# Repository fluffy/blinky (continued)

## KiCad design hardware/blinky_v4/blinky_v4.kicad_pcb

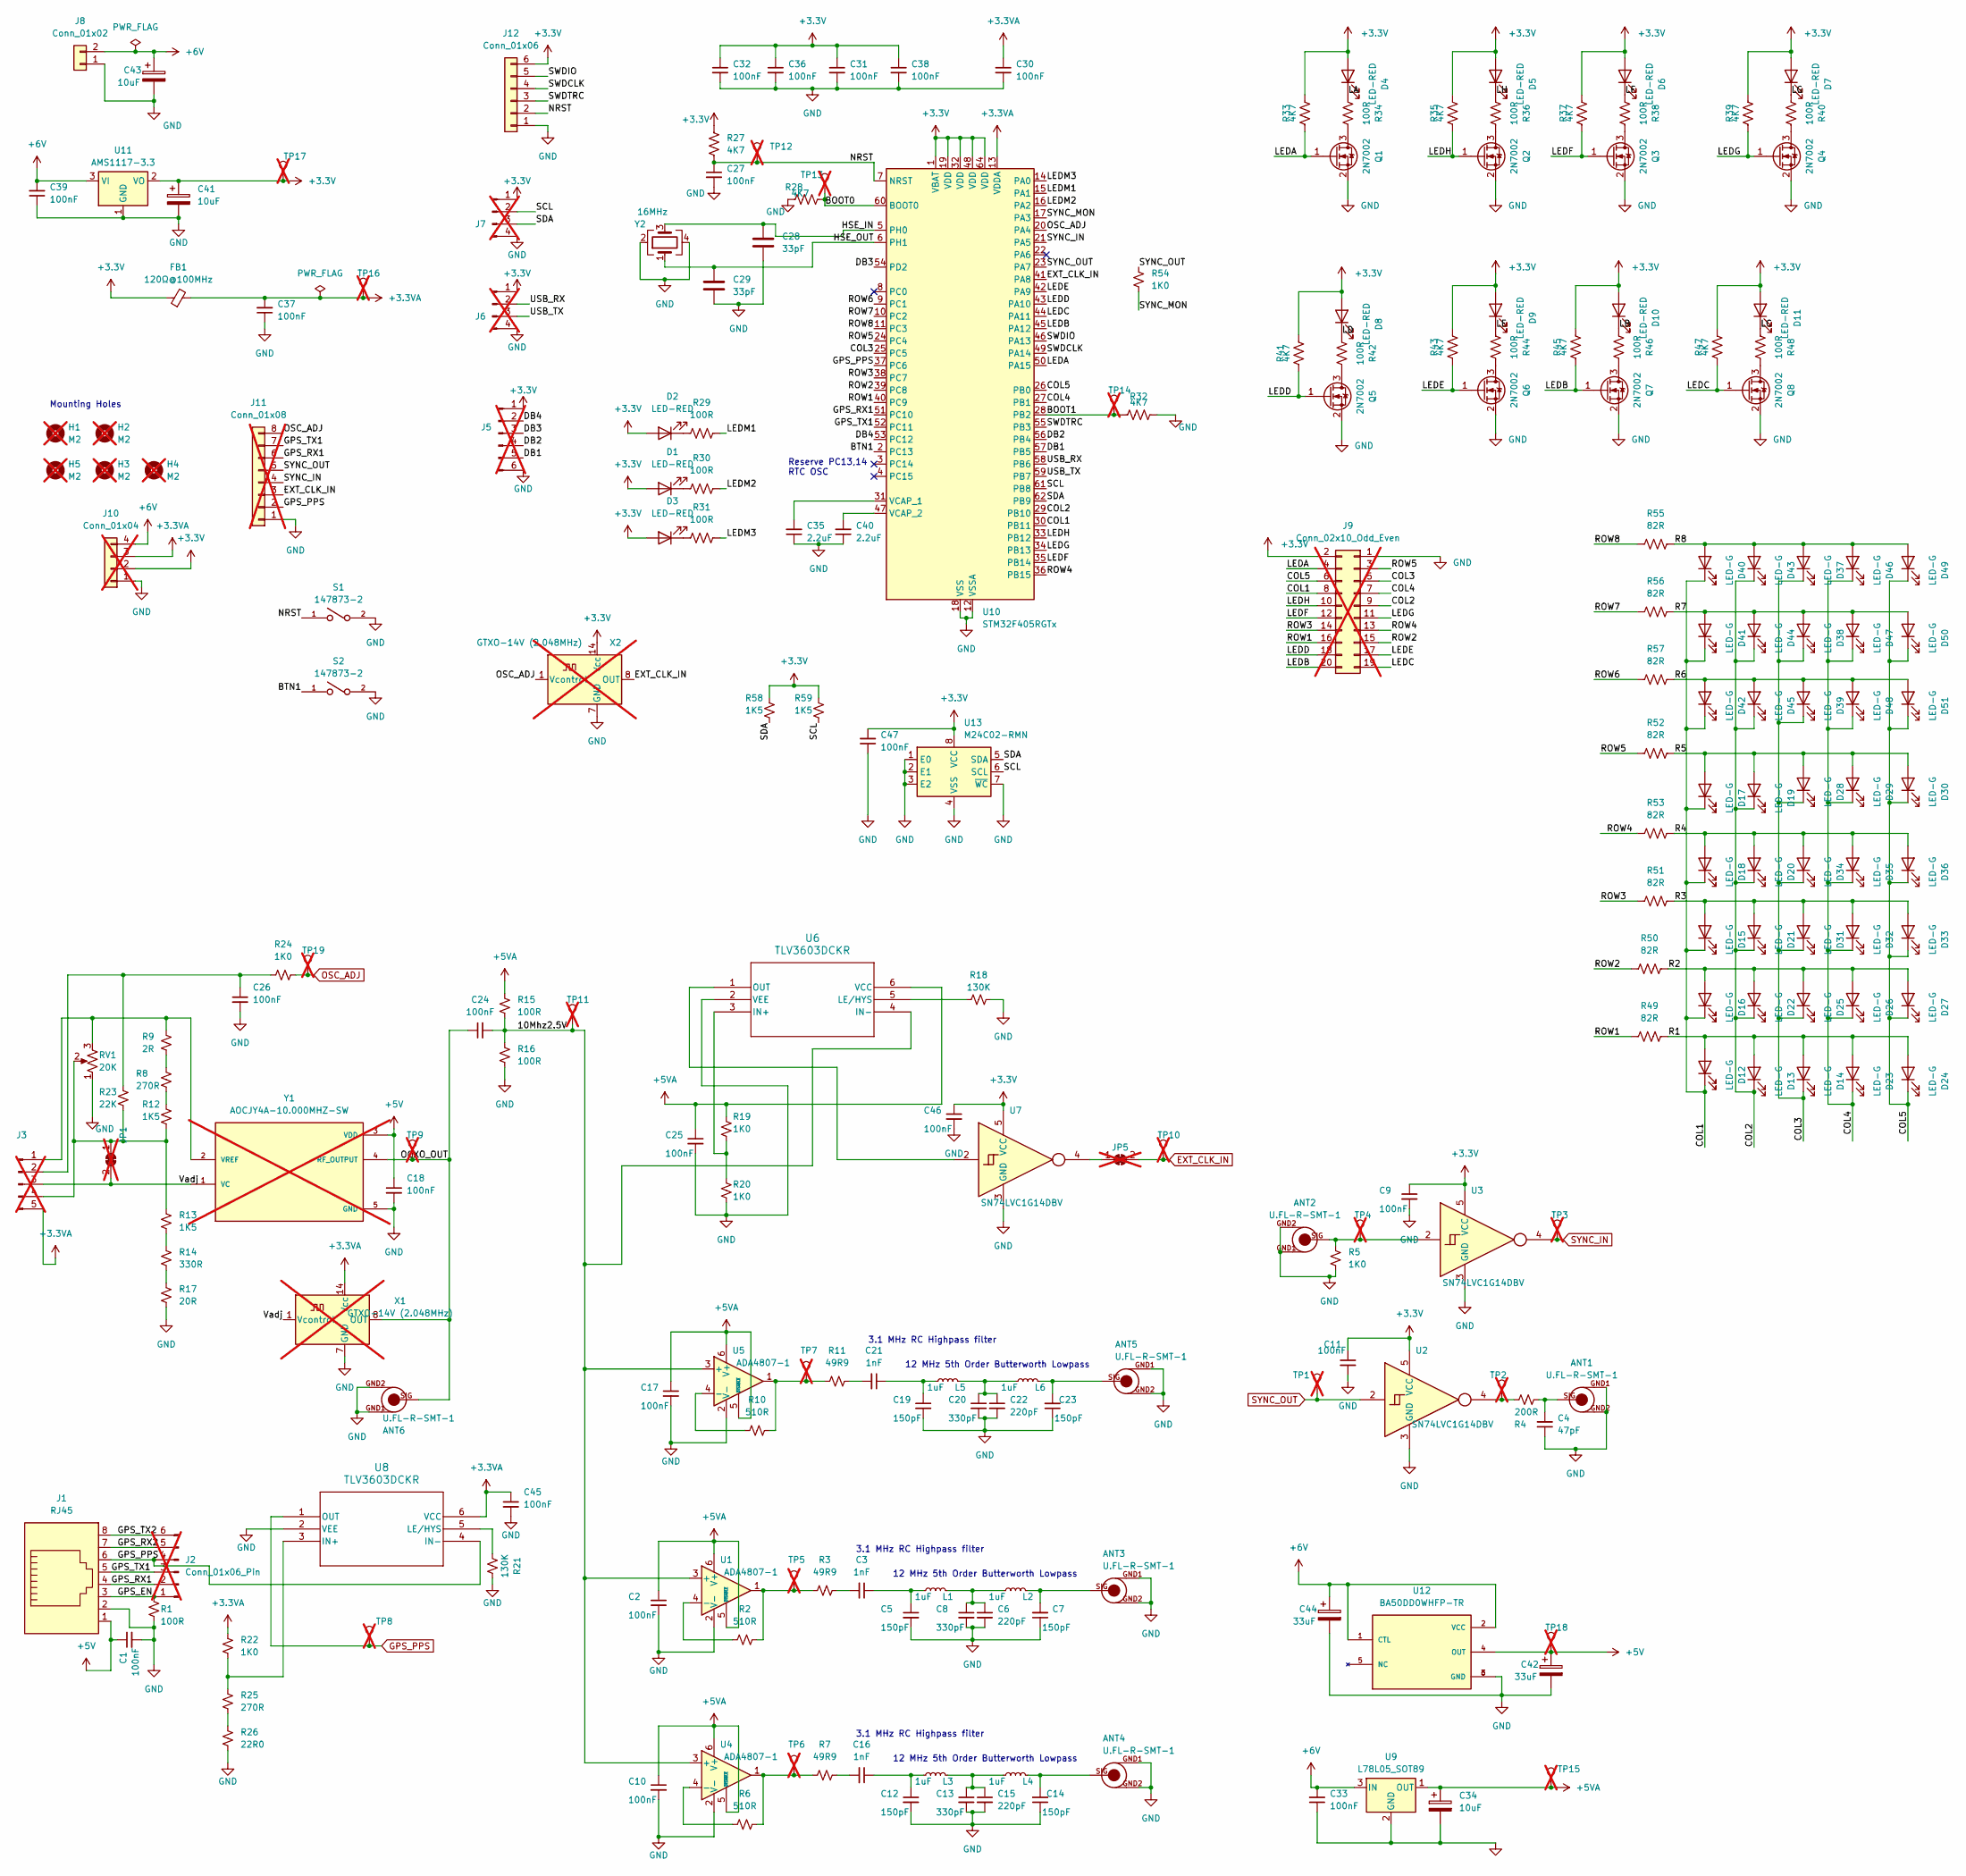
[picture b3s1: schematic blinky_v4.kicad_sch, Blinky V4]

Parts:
ANT1, ANT2, ANT3, ANT4, ANT5, ANT6: U.FL-R-SMT-1; LCSC C88374
C1, C2, C9, C10, C11, C17, C18, C25, C26, C30, C31, C32, C33, C36, C38, C39, C45, C46, C47: 100nF; C_0402_1005Metric; LCSC C307331
C3, C16, C21: 1nF; C_0603_1608Metric; LCSC C1588
C4: 47pF; C_0805_2012Metric; LCSC C14857
C5, C7, C12, C14, C19, C23: 150pF; C_0603_1608Metric; LCSC C1594
C6, C15, C22: 220pF; C_0603_1608Metric; LCSC C1603
C8, C13, C20: 330pF; C_0603_1608Metric; LCSC C1664
C24, C27, C37: 100nF; C_0603_1608Metric; LCSC C14663
C28, C29: 33pF; C_0603_1608Metric; LCSC C1663
C34, C41, C43: 10uF; CP_EIA-3216-18_Kemet-A; LCSC C7171
C35, C40: 2.2uF; C_0603_1608Metric; LCSC C23630
C42, C44: 33uF; CP_EIA-3528-21_Kemet-B; LCSC C128342
D1, D2, D3, D4, D5, D6, D7, D8, D9, D10, D11: LED-RED; LED_0603_1608Metric; LCSC C94869
D12, D13, D14, D15, D16, D17, D18, D19, D20, D21, D22, D23, D24, D25, D26, D27, D28, D29, D30, D31, D32, D33, D34, D35, D36, D37, D38, D39, D40, D41, D42, D43, D44, D45, D46, D47, D48, D49, D50, D51: LED-G; LED_0603_1608Metric; LCSC C125093
FB1: 120Ω@100MHz; R_0603_1608Metric; LCSC C127301
H1, H2, H3, H4, H5: M2; MountingHole_2.2mm_M2; not fitted
J1: RJ45; RJ45_Amphenol_RJHSE5380; LCSC C464586
J2, J5: Conn_01x06_Pin; PinHeader_1x06_P2.54mm_Vertical; not fitted
J3: Conn_01x05_Pin; PinHeader_1x05_P2.54mm_Vertical; not fitted
J6, J7: Conn_01x04_Pin; PinHeader_1x04_P2.54mm_Vertical; not fitted
J8: Conn_01x02; JST_PH_S2B-PH-SM4-TB_1x02-1MP_P2.00mm_Horizontal; LCSC C295747
J9: Conn_02x10_Odd_Even; PinHeader_2x10_P2.54mm_Vertical; not fitted
J10: Conn_01x04; PinHeader_1x04_P2.54mm_Vertical; not fitted
J11: Conn_01x08; PinHeader_1x08_P2.54mm_Vertical; not fitted
J12: Conn_01x06; JST_PH_S6B-PH-SM4-TB_1x06-1MP_P2.00mm_Horizontal; LCSC C265405
JP1, JP5: SolderJumper_2_Bridged; SolderJumper-2_P1.3mm_Bridged_RoundedPad1.0x1.5mm; not fitted
L1, L2, L3, L4, L5, L6: 1uF; L_0805_2012Metric; LCSC C1042
Q1, Q2, Q3, Q4, Q5, Q6, Q7, Q8: 2N7002; SOT-23; LCSC C8545
R1, R15, R16, R29, R30, R31, R34, R36, R38, R40, R42, R44, R46, R48: 100R; R_0603_1608Metric; LCSC C22775
R2, R6, R10: 510R; R_0603_1608Metric; LCSC C23193
R3, R7, R11: 49R9; R_0603_1608Metric; LCSC C23185
R4: 200R; R_0805_2012Metric; LCSC C17540
R5, R19, R20, R22, R24, R54: 1K0; R_0603_1608Metric; LCSC C21190
R8: 270R; R_0805_2012Metric; LCSC C17590
R9: 2R; R_0805_2012Metric; LCSC C17606
R12, R13: 1K5; R_0805_2012Metric; LCSC C4310
R14: 330R; R_0805_2012Metric; LCSC C17630
R17: 20R; R_0805_2012Metric; LCSC C17544
R18, R21: 130K; R_0603_1608Metric; LCSC C22795
R23: 22K; R_0805_2012Metric; LCSC C17560
R25: 270R; R_0603_1608Metric; LCSC C22966
R26: 22R0; R_0603_1608Metric; LCSC C23345
R27, R28, R32, R33, R35, R37, R39, R41, R43, R45, R47: 4K7; R_0603_1608Metric; LCSC C23162
R49, R50, R51, R52, R53, R55, R56, R57: 82R; R_0603_1608Metric; LCSC C23255
R58, R59: 1K5; R_0603_1608Metric; LCSC C22843
RV1: 20K; Potentiometer_Bourns_3314G_Vertical; LCSC C780217
S1, S2: 147873-2; SW_147873-2
TP1, TP2, TP3, TP4, TP5, TP6, TP7, TP8, TP9, TP10, TP11, TP12, TP13, TP14, TP15, TP16, TP17, TP18, TP19: TestPoint_THTPad_D1.5mm_Drill0.7mm; not fitted
U1, U4, U5: ADA4807-1; SOT-23-6; LCSC C2058411
U2, U3, U7: SN74LVC1G14DBV; SOT-23-5; LCSC C133145
U6, U8: TLV3603DCKR; SC70_DCK_TEX; LCSC C5213955
U9: L78L05_SOT89; SOT-89-3; LCSC C71136
U10: STM32F405RGTx; LQFP-64_10x10mm_P0.5mm; LCSC C15742
U11: AMS1117-3.3; SOT-223-3_TabPin2; LCSC C6186
U12: BA50DD0WHFP-TR; DPAK172P1054X200-6N; PARTREV 003; LCSC C509718
U13: M24C02-RMN; SOIC-8_3.9x4.9mm_P1.27mm; LCSC C83836
X1, X2: GTXO-14V (2.048MHz); Oscillator_DIP-14; not fitted
Y1: AOCJY4A-10.000MHZ-SW; XTAL_AOCJY4A-10.000MHZ-SW; PARTREV 07.24.11; LCSC C1670487; not fitted
Y2: 16MHz; Crystal_SMD_3225-4Pin_3.2x2.5mm; LCSC C13738

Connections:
+3.3V: C9.1, C11.1, C31.1, C32.1, C36.1, C38.1, C41.1, C46.1, C47.2, D1.2 (A), D2.2 (A), D3.2 (A), D4.2 (A), D5.2 (A), D6.2 (A), D7.2 (A), D8.2 (A), D9.2 (A), D10.2 (A), D11.2 (A), FB1.1, J5.1, J6.1, J7.1, J9.2, J10.2, J12.6, R27.1, R33.1, R35.1, R37.1, R39.1, R41.1, R43.1, R45.1, R47.1, R58.1, R59.1, TP17.1, U2.5 (VCC), U3.5 (VCC), U7.5 (VCC), U10.1 (VBAT), U10.19 (VDD), U10.32 (VDD), U10.48 (VDD), U10.64 (VDD), U11.2 (VO), U13.8 (VCC), X2.14 (Vcc)
+3.3VA: C30.1, C37.2, C45.1, FB1.2, J3.5, J10.3, R22.1, TP16.1, U8.6 (VCC), U10.13 (VDDA), X1.14 (Vcc)
+5V: C1.1, C18.1, C42.1, J1.1, TP18.1, U12.4 (OUT), Y1.3 (VDD)
+5VA: C2.1, C10.1, C17.1, C25.1, C34.1, R15.1, R19.1, TP15.1, U1.5 (~DISABLE), U1.6 (V+), U4.5 (~DISABLE), U4.6 (V+), U5.5 (~DISABLE), U5.6 (V+), U6.6 (VCC), U9.1 (OUT)
+6V: C33.2, C39.2, C43.1, C44.1, J8.2, J10.4, U9.3 (IN), U11.3 (VI), U12.1 (CTL), U12.2 (VCC)
/10Mhz2.5V: C24.2, R15.2, R16.1, TP11.1, U1.3 (+), U4.3 (+), U5.3 (+), U6.4 (IN-)
/BOOT0: R28.1, TP13.1, U10.60 (BOOT0)
/BOOT1: R32.2, TP14.1, U10.28 (PB2)
/BTN1: S2.1, U10.2 (PC13)
/COL1: D12.1 (K), D15.1 (K), D16.1 (K), D17.1 (K), D18.1 (K), D40.1 (K), D41.1 (K), D42.1 (K), J9.8, U10.30 (PB11)
/COL2: D13.1 (K), D19.1 (K), D20.1 (K), D21.1 (K), D22.1 (K), D43.1 (K), D44.1 (K), D45.1 (K), J9.9, U10.29 (PB10)
/COL3: D14.1 (K), D25.1 (K), D28.1 (K), D31.1 (K), D34.1 (K), D37.1 (K), D38.1 (K), D39.1 (K), J9.5, U10.25 (PC5)
/COL4: D23.1 (K), D26.1 (K), D29.1 (K), D32.1 (K), D35.1 (K), D46.1 (K), D47.1 (K), D48.1 (K), J9.7, U10.27 (PB1)
/COL5: D24.1 (K), D27.1 (K), D30.1 (K), D33.1 (K), D36.1 (K), D49.1 (K), D50.1 (K), D51.1 (K), J9.6, U10.26 (PB0)
/DB1: J5.5, U10.57 (PB5)
/DB2: J5.4, U10.56 (PB4)
/DB3: J5.3, U10.54 (PD2)
/DB4: J5.2, U10.53 (PC12)
/GPS_EN: J1.3, J2.1, R1.1
/GPS_RX1: J1.4, J2.2, J11.6, U10.51 (PC10)
/GPS_RX2: J1.7, J2.5
/GPS_TX1: J1.5, J2.3, J11.7, U10.52 (PC11)
/GPS_TX2: J1.8, J2.6
/HSE_IN: C28.1, U10.5 (PH0), Y2.3
/HSE_OUT: C29.1, U10.6 (PH1), Y2.1
/LA: D4.1 (K), R34.1
/LB: D10.1 (K), R46.1
/LC: D11.1 (K), R48.1
/LD: D8.1 (K), R42.1
/LE: D9.1 (K), R44.1
/LEDA: J9.4, Q1.1 (G), R33.2, U10.50 (PA15)
/LEDB: J9.20, Q7.1 (G), R45.2, U10.45 (PA12)
/LEDC: J9.19, Q8.1 (G), R47.2, U10.44 (PA11)
/LEDD: J9.18, Q5.1 (G), R41.2, U10.43 (PA10)
/LEDE: J9.17, Q6.1 (G), R43.2, U10.42 (PA9)
/LEDF: J9.12, Q3.1 (G), R37.2, U10.35 (PB14)
/LEDG: J9.11, Q4.1 (G), R39.2, U10.34 (PB13)
/LEDH: J9.10, Q2.1 (G), R35.2, U10.33 (PB12)
/LEDM1: R29.2, U10.15 (PA1)
/LEDM2: R30.2, U10.16 (PA2)
/LEDM3: R31.2, U10.14 (PA0)
/LF: D6.1 (K), R38.1
/LG: D7.1 (K), R40.1
/LH: D5.1 (K), R36.1
/NRST: C27.1, J12.2, R27.2, S1.1, TP12.1, U10.7 (NRST)
/OCXO_OUT: ANT6.SIG, C24.1, TP9.1, X1.8 (OUT), Y1.4 (RF_OUTPUT)
/R1: D12.2 (A), D13.2 (A), D14.2 (A), D23.2 (A), D24.2 (A), R49.1
/R2: D16.2 (A), D22.2 (A), D25.2 (A), D26.2 (A), D27.2 (A), R50.1
/R3: D15.2 (A), D21.2 (A), D31.2 (A), D32.2 (A), D33.2 (A), R51.1
/R4: D18.2 (A), D20.2 (A), D34.2 (A), D35.2 (A), D36.2 (A), R53.1
/R5: D17.2 (A), D19.2 (A), D28.2 (A), D29.2 (A), D30.2 (A), R52.1
/R6: D39.2 (A), D42.2 (A), D45.2 (A), D48.2 (A), D51.2 (A), R57.1
/R7: D38.2 (A), D41.2 (A), D44.2 (A), D47.2 (A), D50.2 (A), R56.1
/R8: D37.2 (A), D40.2 (A), D43.2 (A), D46.2 (A), D49.2 (A), R55.1
/ROW1: J9.16, R49.2, U10.40 (PC9)
/ROW2: J9.15, R50.2, U10.39 (PC8)
/ROW3: J9.14, R51.2, U10.38 (PC7)
/ROW4: J9.13, R53.2, U10.36 (PB15)
/ROW5: J9.3, R52.2, U10.24 (PC4)
/ROW6: R57.2, U10.9 (PC1)
/ROW7: R56.2, U10.10 (PC2)
/ROW8: R55.2, U10.11 (PC3)
/SCL: J7.2, R59.2, U10.61 (PB8), U13.6 (SCL)
/SDA: J7.3, R58.2, U10.62 (PB9), U13.5 (SDA)
/SWDCLK: J12.4, U10.49 (PA14)
/SWDIO: J12.5, U10.46 (PA13)
/SWDTRC: J12.3, U10.55 (PB3)
/SYNC_MON: R54.2, U10.17 (PA3)
/USB_RX: J6.2, U10.58 (PB6)
/USB_TX: J6.3, U10.59 (PB7)
/Vadj: J3.3, JP1.2 (B), X1.1 (Vcontrol), Y1.1 (VC)
EXT_CLK_IN: J11.3, JP5.2 (B), TP10.1, U10.41 (PA8), X2.8 (OUT)
GND: ANT1.GND1, ANT1.GND2, ANT2.GND1, ANT2.GND2, ANT3.GND1, ANT3.GND2, ANT4.GND1, ANT4.GND2, ANT5.GND1, ANT5.GND2, ANT6.GND1, ANT6.GND2, C1.2, C2.2, C4.1, C5.2, C6.2, C7.1, C8.2, C9.2, C10.2, C11.2, C12.2, C13.2, C14.1, C15.2, C17.2, C18.2, C19.2, C20.2, C22.2, C23.1, C25.2, C26.2, C27.2, C28.2, C29.2, C30.2, C31.2, C32.2, C33.1, C34.2, C35.1, C36.2, C37.1, C38.2, C39.1, C40.1, C41.2, C42.2, C43.2, C44.2, C45.2, C46.2, C47.1, J1.2, J5.6, J6.4, J7.4, J8.1, J9.1, J10.1, J11.1, J12.1, Q1.2 (S), Q2.2 (S), Q3.2 (S), Q4.2 (S), Q5.2 (S), Q6.2 (S), Q7.2 (S), Q8.2 (S), R1.2, R5.2, R16.2, R17.2, R18.2, R20.2, R21.2, R26.2, R28.2, R32.1, RV1.1, S1.2, S2.2, U1.2 (V-), U2.3 (GND), U3.3 (GND), U4.2 (V-), U5.2 (V-), U6.2 (VEE), U7.3 (GND), U8.2 (VEE), U9.2 (GND), U10.12 (VSSA), U10.18 (VSS), U10.63 (VSS), U11.1 (GND), U12.3 (GND), U12.6 (GND), U13.1 (E0), U13.2 (E1), U13.3 (E2), U13.4 (VSS), U13.7 (~WC), X1.7 (GND), X2.7 (GND), Y1.5 (GND), Y2.2, Y2.4
GPS_PPS: J1.6, J2.4, J11.2, TP8.1, U8.1 (OUT), U8.4 (IN-), U10.37 (PC6)
unnamed: ANT1.SIG, C4.2, R4.2
unnamed: ANT2.SIG, R5.1, TP4.1, U3.2
unnamed: ANT3.SIG, C7.2, L2.1
unnamed: ANT4.SIG, C14.2, L4.1
unnamed: ANT5.SIG, C23.2, L6.1
unnamed: C3.1, C5.1, L1.1
unnamed: C3.2, R3.2
unnamed: C6.1, C8.1, L1.2, L2.2
unnamed: C12.1, C16.1, L3.1
unnamed: C13.1, C15.1, L3.2, L4.2
unnamed: C16.2, R7.2
unnamed: C19.1, C21.1, L5.1
unnamed: C20.1, C22.1, L5.2, L6.2
unnamed: C21.2, R11.2
unnamed: D1.1 (K), R30.1
unnamed: D2.1 (K), R29.1
unnamed: D3.1 (K), R31.1
unnamed: J3.1, R9.1, RV1.3, Y1.2 (VREF)
unnamed: C26.1, J3.2, R23.1, R24.1
unnamed: J3.4, JP1.1 (A), R12.2, R13.1, R23.2, RV1.2
unnamed: JP5.1 (A), U7.4
unnamed: Q1.3 (D), R34.2
unnamed: Q2.3 (D), R36.2
unnamed: Q3.3 (D), R38.2
unnamed: Q4.3 (D), R40.2
unnamed: Q5.3 (D), R42.2
unnamed: Q6.3 (D), R44.2
unnamed: Q7.3 (D), R46.2
unnamed: Q8.3 (D), R48.2
unnamed: R2.2, R3.1, TP5.1, U1.1
unnamed: R4.1, TP2.1, U2.4
unnamed: R6.2, R7.1, TP6.1, U4.1
unnamed: R8.1, R9.2
unnamed: R10.2, R11.1, TP7.1, U5.1
unnamed: R8.2, R12.1
unnamed: R13.2, R14.1
unnamed: R14.2, R17.1
unnamed: R25.2, R26.1
unnamed: R2.1, U1.4 (-)
unnamed: R6.1, U4.4 (-)
unnamed: R10.1, U5.4 (-)
unnamed: R19.2, R20.1, U6.3 (IN+)
unnamed: R18.1, U6.5 (LE/HYS)
unnamed: U6.1 (OUT), U7.2
unnamed: R22.2, R25.1, U8.3 (IN+)
unnamed: R21.1, U8.5 (LE/HYS)
unnamed: C35.2, U10.31 (VCAP_1)
unnamed: C40.2, U10.47 (VCAP_2)
OSC_ADJ: J11.8, R24.2, TP19.1, U10.20 (PA4), X2.1 (Vcontrol)
SYNC_IN: J11.4, TP3.1, U3.4, U10.21 (PA5)
SYNC_OUT: J11.5, R54.1, TP1.1, U2.2, U10.23 (PA7)

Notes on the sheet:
3.1 MHz RC Highpass filter
Reserve PC13,14 RTC OSC
12 MHz 5th Order Butterworth Lowpass
Mounting Holes

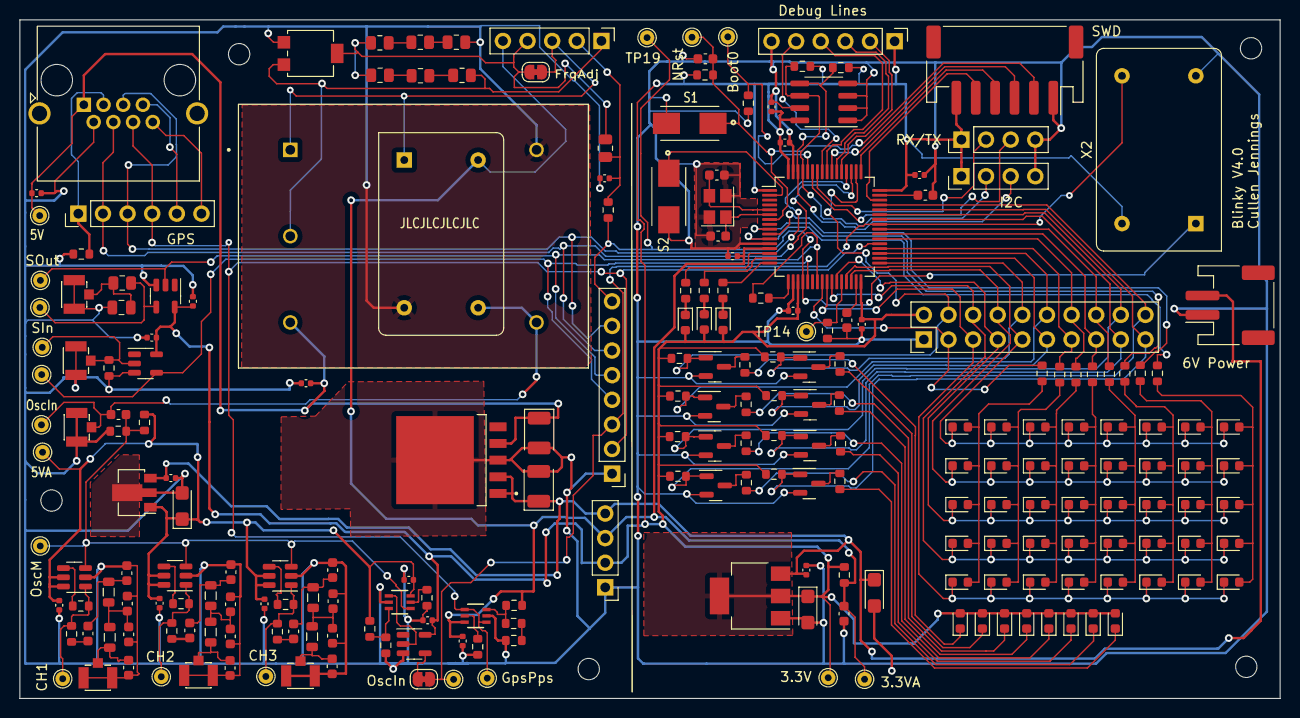
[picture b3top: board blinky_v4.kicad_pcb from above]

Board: 2 copper layers, 130.0 x 70.0 mm, 235 parts (0 on the bottom side), 125 nets.

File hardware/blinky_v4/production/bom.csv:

Designator,Footprint,Quantity,Value,LCSC Part #
"ANT1, ANT2, ANT3, ANT4, ANT5, ANT6",U.FL-R-SMT-1,6,U.FL-R-SMT-1,C88374
"C1, C10, C11, C17, C18, C2, C25, C26, C30, C31, C32, C33, C36, C38, C39, C45, C46, C47, C9",0402,19,100nF,C307331
"C12, C14, C19, C23, C5, C7",0603,6,150pF,C1594
"C13, C20, C8",0603,3,330pF,C1664
"C15, C22, C6",0603,3,220pF,C1603
"C16, C21, C3",0603,3,1nF,C1588
"C24, C27, C37",0603,3,100nF,C14663
"C28, C29",0603,2,33pF,C1663
"C34, C41, C43",CP_EIA-3216-18_Kemet-A,3,10uF,C7171
"C35, C40",0603,2,2.2uF,C23630
C4,0805,1,47pF,C14857
"C42, C44",CP_EIA-3528-21_Kemet-B,2,33uF,C128342
"D1, D10, D11, D2, D3, D4, D5, D6, D7, D8, D9",0603,11,LED-RED,C94869
"D12, D13, D14, D15, D16, D17, D18, D19, D20, D21, D22, D23, D24, D25, D26, D27, D28, D29, D30, D31, D32, D33, D34, D35, D36, D37, D38, D39, D40, D41, D42, D43, D44, D45, D46, D47, D48, D49, D50, D51",0603,40,LED-G,C125093
FB1,0603,1,120Ω@100MHz ,C127301
J1,RJ45_Amphenol_RJHSE5380,1,RJ45,C464586
J12,JST_PH_S6B-PH-SM4-TB_1x06-1MP_P2.00mm_Horizontal,1,Conn_01x06,C265405
J8,JST_PH_S2B-PH-SM4-TB_1x02-1MP_P2.00mm_Horizontal,1,Conn_01x02,C295747
"L1, L2, L3, L4, L5, L6",0805,6,1uF,C1042
"Q1, Q2, Q3, Q4, Q5, Q6, Q7, Q8",SOT-23,8,2N7002,C8545
"R1, R15, R16, R29, R30, R31, R34, R36, R38, R40, R42, R44, R46, R48",0603,14,100R,C22775
"R10, R2, R6",0603,3,510R,C23193
"R11, R3, R7",0603,3,49R9,C23185
"R12, R13",0805,2,1K5,C4310
R14,0805,1,330R,C17630
R17,0805,1,20R,C17544
"R18, R21",0603,2,130K,C22795
"R19, R20, R22, R24, R5, R54",0603,6,1K0,C21190
R23,0805,1,22K,C17560
R25,0603,1,270R,C22966
R26,0603,1,22R0,C23345
"R27, R28, R32, R33, R35, R37, R39, R41, R43, R45, R47",0603,11,4K7,C23162
R4,0805,1,200R,C17540
"R49, R50, R51, R52, R53, R55, R56, R57",0603,8,82R,C23255
"R58, R59",0603,2,1K5,C22843
R8,0805,1,270R,C17590
R9,0805,1,2R,C17606
RV1,Potentiometer_Bourns_3314G_Vertical,1,20K,C780217
"S1, S2",SW_147873-2,2,147873-2,
"U1, U4, U5",SOT-23-6,3,ADA4807-1,C2058411
U10,LQFP-64_10x10mm_P0.5mm,1,STM32F405RGTx,C15742
U11,SOT-223-3_TabPin2,1,AMS1117-3.3,C6186
U12,DPAK172P1054X200-6N,1,BA50DD0WHFP-TR,C509718
U13,SOIC-8_3.9x4.9mm_P1.27mm,1,M24C02-RMN,C83836
"U2, U3, U7",SOT-23-5,3,SN74LVC1G14DBV,C133145
"U6, U8",SC70_DCK_TEX,2,TLV3603DCKR,C5213955
U9,SOT-89-3,1,L78L05_SOT89,C71136
Y2,Crystal_SMD_3225-4Pin_3.2x2.5mm,1,16MHz ,C13738
